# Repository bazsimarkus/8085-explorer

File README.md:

# 8085-explorer

A Netronics Explorer/85 compatible Intel 8085 single board computer that runs the original Microsoft ROM BASIC v4.7, the original Netronics Explorer/85 monitor ROM, and a custom MicroPython interpreter written entirely in 8085 assembly. Software compatible with the 1979 original, built from a minimal number of through-hole chips, and easy to assemble.

---

## Table of Contents

- [Overview](#overview)
- [Features](#features)
- [Getting Started](#getting-started)
  - [What You Need](#what-you-need)
  - [Flashing the ROM](#flashing-the-rom)
  - [Connecting](#connecting)
  - [Starting BASIC](#starting-basic)
- [MicroPython Interpreter](#micropython-interpreter)
  - [About](#about)
  - [Running MicroPython](#running-micropython)
  - [MicroPython Features](#micropython-features)
  - [Building from Source](#building-from-source)
- [Examples](#examples)
  - [Microsoft BASIC Examples](#microsoft-basic-examples)
  - [MicroPython Examples](#micropython-examples)
  - [Assembly Examples](#assembly-examples)
- [Schematic](#schematic)
  - [Bill of Materials](#bill-of-materials)
- [How It Works](#how-it-works)
  - [Address Bus Demultiplexing](#address-bus-demultiplexing)
  - [Memory Map](#memory-map)
  - [The Boot Problem and the Glue Logic](#the-boot-problem-and-the-glue-logic)
  - [Serial Communication](#serial-communication)
- [Documentation](#documentation)
- [Acknowledgments](#acknowledgments)
- [License](#license)

---

## Overview

The 8085 Explorer is a single board computer built around the Intel 8085 microprocessor. It is software compatible with the original Netronics Explorer/85 from 1979 and runs the same monitor ROM and Microsoft BASIC that shipped with the original kit. The board uses a small number of readily available through-hole chips and communicates through an RS232 serial port. Connect it to a terminal emulator like Tera Term and you have a working retro computer that boots into a machine language monitor and can run BASIC programs interactively.

In addition to the classic Microsoft BASIC environment, the board can also run a custom MicroPython interpreter written from scratch in 8085 assembly. Flash a different ROM image and the board boots into a Python-like interactive shell instead.

The design was inspired by Tom Nisbet's [Simple8085](https://github.com/TomNisbet/Simple8085). I used his [TommyPROM](https://github.com/TomNisbet/TommyPROM) programmer to flash the ROM image onto the 28C256 EEPROM.

---

## Features

- Intel 8085 CPU running at 3.072 MHz (6.144 MHz crystal divided by 2)
- 32K ROM (28C256 EEPROM) containing the Netronics monitor and Microsoft BASIC
- 32K Static RAM (HM62256BLP)
- RS232 serial port via MAX232 level converter and DB9 connector
- Bit-banged serial I/O using the 8085's SID and SOD pins
- Original Netronics Explorer/85 monitor ROM v1.4
- Microsoft ROM BASIC v4.7 (Copyright 1978 by Microsoft)
- Custom MicroPython interpreter (written in 8085 assembly, runs from a separate ROM image)
- Minimal chip count, all through-hole, easy to build on a soldering iron
- 9V DC barrel jack power input with L7805 5V regulator
- Power on reset with manual reset button
- Power LED, serial RX and TX activity LEDs
- Expansion header and SID/SOD pin headers
- Designed in KiCad, full schematic and PCB files included

---

## Getting Started

### What You Need

- The assembled 8085 Explorer board
- A 9V DC power supply (center positive, 2.1mm barrel jack)
- A DB9 serial cable or USB-to-RS232 adapter
- A terminal emulator (Tera Term, PuTTY, minicom, etc.)
- An EEPROM programmer for flashing the 28C256 (e.g. [TommyPROM](https://github.com/TomNisbet/TommyPROM))

### Flashing the ROM

The file `assets/msbasic47-rom-image.bin` contains the combined ROM image with both the Netronics monitor and Microsoft BASIC. Flash this file onto a 28C256 EEPROM using your programmer of choice.

Alternatively, flash `assets/micropython85/micropython85-rom-image.bin` to run the MicroPython interpreter instead.

### Connecting

1. Configure your terminal emulator for **9600 baud, 8 data bits, no parity, 1 stop bit (9600 8N1)**.
2. Connect the serial cable between the board's DB9 port and your computer.
3. Flip the power switch on.
4. If using the Microsoft BASIC ROM: press the Space key once. The monitor ROM uses this first character to auto-detect the baud rate. Nothing will appear on screen until you do this.
5. If using the MicroPython ROM: the interpreter boots directly and presents a `>>>` prompt.

After pressing Space (with the BASIC ROM), you should see the Explorer/85 monitor banner:

```
EXPLORER-85    VER 1.4
Copyright 1979
Netronics R&D
New Milford, CT.
```

### Starting BASIC

From the monitor prompt, configure the memory map and jump to BASIC:

```
.XS 44FF-7800 FFFF-C000
.G
```

BASIC will ask for memory size and terminal width. Press Enter to accept the defaults, or type values:

```
Memory size? 30000
Terminal width? 72
Microsoft ROM BASIC Ver 4.7
Copyright (C) 1978 by Microsoft
29443 Bytes free
Ok
```

You are now in BASIC and can write and run programs interactively.

Note: In my experience there is no whitespace between a monitor command and its parameter. For example, `GC000` starts BASIC (jumps to address C000h), not `G C000`.

---

## MicroPython Interpreter

### About

The MicroPython interpreter is a minimal Python-like environment written entirely in 8085 assembly. It is not a port of the official MicroPython project. It is a from-scratch implementation that provides a familiar interactive experience on an 8-bit processor with no operating system.

The interpreter lives in a separate ROM image. You swap between Microsoft BASIC and MicroPython by flashing a different binary onto the 28C256.

### Running MicroPython

Flash `assets/micropython85/micropython85-rom-image.bin` onto your 28C256, insert the chip, and power on. The board boots directly into the REPL:

```
8085-Explorer Booting...
Memory Swap Successful: ROM@8000, RAM@0000
Booting MicroPython v1.20.0-8085 on 2026-05-10; 8085-Explorer with i8085
Type "help()" for more information.

>>> print("Hello world!")
Hello world!
>>>
```

### MicroPython Features

- Interactive REPL with `>>>` prompt and `...` continuation for blocks
- 26 variables (a through z), each a 16-bit signed integer
- Arithmetic: `+` `-` `*` `/` `//` `**` `%`
- Comparisons: `>` `<` `>=` `<=` `==` `!=`
- `print()` with string literals and numeric expressions, comma-separated
- `if/else` blocks with indentation
- `for i in range(n)` and `for i in range(start, stop)` loops
- `help()` built-in
- Comments with `#`
- Error reporting: `SyntaxError` and `ZeroDivisionError`

### Building from Source

The full source is at `assets/micropython85/micropython85.asm`. Assemble it with [Tom Nisbet's asm85](https://github.com/TomNisbet/asm85):

```
asm85 -b 8000:ffff micropython85.asm
```

This produces the binary ROM image ready for flashing.

---

## Examples

The `examples/` directory contains programs for the three levels of the system.

### Microsoft BASIC Examples

Located in `examples/basic/`. These programs are typed in (or pasted) at the `Ok` prompt when the board is running the Microsoft ROM BASIC image.

### MicroPython Examples

Located in `examples/micropython/`. These scripts are typed in (or pasted) at the `>>>` prompt when the board is running the MicroPython interpreter ROM image.

### Assembly Examples

Located in `examples/assembly/`. These are standalone 8085 assembly programs that get assembled with [asm85](https://github.com/TomNisbet/asm85) and flashed directly onto the 28C256. Unlike the BASIC and MicroPython examples (which run inside their respective interpreters), assembly programs replace the entire ROM content and run on bare hardware.

To build and flash:

```
asm85 -b 8000:ffff yourprogram.asm
```

Then program the resulting binary onto a 28C256 EEPROM.

---

## Schematic

The full KiCad project files (schematic, PCB layout, and project file) are in the `schematic/` directory.

### Bill of Materials

The following table lists all components needed to build one complete 8085 Explorer board.

#### PCB

| Ref | Qty | Description |
|-----|-----|-------------|
| - | 1 | 8085 Explorer v1.0 PCB |

#### Integrated Circuits

| Ref | Qty | Value | Package |
|-----|-----|-------|---------|
| U1 | 1 | 8085 | DIP-40 |
| U2 | 1 | 74LS573 | DIP-20 |
| U3 | 1 | 28C256 EEPROM | DIP-28 |
| U4 | 1 | HM62256BLP SRAM | DIP-28 |
| U5 | 1 | 74LS14 | DIP-14 |
| U6 | 1 | 74LS32 | DIP-14 |
| U7 | 1 | 74LS74 | DIP-14 |
| U8 | 1 | MAX232 | DIP-16 |
| U9 | 1 | L7805 voltage regulator | TO-220 |

#### IC Sockets

| Qty | Description |
|-----|-------------|
| 1 | 40-pin DIP socket (for U1) |
| 1 | 20-pin DIP socket (for U2) |
| 2 | 28-pin DIP socket (for U3, U4) |
| 3 | 14-pin DIP socket (for U5, U6, U7) |
| 1 | 16-pin DIP socket (for U8) |

#### Capacitors

| Ref | Qty | Value | Type |
|-----|-----|-------|------|
| C1-C7, C17 | 7 | 100nF | Ceramic |
| C8 | 1 | 22pF | Ceramic |
| C9 | 1 | 47uF | Electrolytic |
| C10-C14 | 5 | 1uF | Electrolytic |
| C15, C18 | 2 | 10uF | Electrolytic |
| C16 | 1 | 330nF | Ceramic |

#### Resistors

| Ref | Qty | Value |
|-----|-----|-------|
| R1, R2, R6 | 3 | 1k |
| R3, R4, R5 | 3 | 10k |

#### Diodes & LEDs

| Ref | Qty | Value |
|-----|-----|-------|
| D1 | 1 | LED 5mm Yellow |
| D2 | 1 | LED 5mm Green |
| D3, D5 | 2 | 1N4001 |
| D4 | 1 | LED 5mm Red |

#### Crystal

| Ref | Qty | Value |
|-----|-----|-------|
| Y1 | 1 | 6.144 MHz (HC49-U) |

#### Connectors & Switches

| Ref | Qty | Description |
|-----|-----|-------------|
| J1 | 1 | DB9 female connector (DE9, right-angle PCB mount) |
| J2 | 1 | DC-005 barrel jack (2.1mm center positive) |
| J4, J5 | 2 | 1x2 pin header (2.54mm) |
| J6 | 1 | 2x5 pin socket (2.54mm, expansion header) |
| S1 | 1 | Tactile push button 6x6mm (reset) |
| S2 | 1 | Toggle switch 7x7mm (power) |

#### Thermal Management

| Qty | Description |
|-----|-------------|
| 1 | Heatsink for TO-220 (for L7805 U9) |

#### External / Off-Board Items

| Qty | Description |
|-----|-------------|
| 1 | 9V DC power supply (center positive, 2.1mm barrel jack) |
| 1 | RS-232 to USB cable (DB9 male to USB-A) |
| 4 | Rubber feet, 3M SJ61A6 |

---

## How It Works

The 8085 Explorer uses a small amount of glue logic to decode memory addresses and manage access to the ROM and RAM chips. If you are new to computer hardware, the following sections explain every piece of the design.

### Address Bus Demultiplexing

The 8085 multiplexes the lower 8 bits of the address bus (A0 to A7) with the data bus (D0 to D7) on the same physical pins. A 74LS573 octal latch (U2) captures the lower address bits when the ALE (Address Latch Enable) signal goes high. After the latch captures them, the bus is free to carry data. This gives us a full 16-bit address bus separated from the 8-bit data bus.

### Memory Map

Once the boot sequence is complete (see below), the memory is split into two halves using address line A15:

- `0000h` to `7FFFh` : 32K RAM (HM62256BLP)
- `8000h` to `FFFFh` : 32K ROM (28C256 EEPROM)

When A15 is low, RAM is selected. When A15 is high, ROM is selected. The monitor lives at F800h and Microsoft BASIC starts at C000h, both in the upper ROM half.

### The Boot Problem and the Glue Logic

If you are a beginner, your first instinct might be: just wire A15 directly to the chip enable pins, select ROM when A15 is high, select RAM when A15 is low. That would work for normal operation. But it creates a problem at startup.

When the 8085 resets, it always fetches its first instruction from address 0000h. If RAM is at 0000h, the CPU reads random garbage from the uninitialized RAM and crashes immediately. The CPU must see ROM at address 0000h when it first powers on.

But we cannot permanently place ROM at 0000h either. Microsoft BASIC and other 8080/8085 software assume that RAM starts at address 0000h. They use the lowest addresses for the stack, variables, and hardware interrupt vectors. If ROM occupied the bottom of memory permanently, BASIC would try to write its variables into ROM and fail.

So we have two conflicting requirements:
1. ROM must be at 0000h at power-on so the CPU can boot.
2. RAM must be at 0000h during normal operation so software works correctly.

The glue logic on this board solves this with a temporary override at reset.

**The Reset Condition Flip-Flop (U7, 74LS74)**

A 74LS74 D flip-flop acts as a one-bit "boot mode" flag. When the CPU resets, its RESET_OUT signal clocks the flip-flop, forcing its Q output high. As long as Q is high, the system is in boot mode.

**Boot Mode Behavior (U6, 74LS32 OR gates and U5, 74LS14 inverters)**

The OR gates enforce this rule: ROM is selected if the flip-flop is set OR if A15 is high. RAM is selected only when neither condition is true. The IO/M signal from the CPU disables both memory chips during I/O operations.

So at power-on, with the flip-flop set, the logic forces ROM to be active regardless of A15. The CPU asks for address 0000h and gets ROM. The first instruction in the ROM image is a jump to address F800h (where the monitor actually lives in the upper half of memory).

**Exiting Boot Mode**

When the CPU executes that jump and reads from the upper memory (A15 goes high), the logic detects a read operation with A15 high and clears the flip-flop. Boot mode ends. From this point forward, A15 alone controls memory selection: low for RAM, high for ROM.

Because the CPU is already executing code in the ROM at F800h, it does not notice that the bottom 32K just switched from ROM to RAM. The memory map is now in its normal configuration. When you later type `GC000` to start BASIC, BASIC wakes up, scans the lower memory, finds 32K of RAM starting at 0000h, and uses it for your programs and variables.

Without these few logic gates and the flip-flop, classic 8085 software like Microsoft BASIC simply would not work on this board.

### Serial Communication

Serial communication is handled through the 8085's built-in SID (Serial Input Data) and SOD (Serial Output Data) pins. The monitor ROM implements a bit-banged UART in software. A MAX232 chip (U8) converts the TTL level signals to proper RS232 voltage levels for the DB9 connector.

The monitor does not use a fixed baud rate. Instead, after reset it waits for you to press the Space key and measures the timing of that character to auto-detect the baud rate. This means the board works at whatever speed your terminal is configured for. I use 9600 bps.

The MicroPython interpreter ROM uses its own bit-banged serial routines hardcoded to 9600 baud (tuned for the 6.144 MHz crystal). It does not require a Space keypress at startup.

---

## Documentation

The `docs/netronics-explorer-85/` directory contains scanned original documentation and photos from the Netronics Explorer/85:

- Original manual pages (Netronics_Explorer85_A through E)
- Terminal ROM user information
- Cabinet assembly instructions and photos
- Original ROM images for the monitor (`explorer_monitor_rom/EXPLORER.HEX`) and BASIC (`explorer_basic_roms/C000.HEX` through `D800.HEX`) as separate files matching the smaller ROM chips used in the original hardware

---

## Acknowledgments

- Tom Nisbet for [Simple8085](https://github.com/TomNisbet/Simple8085), which was the main inspiration for this project, for [TommyPROM](https://github.com/TomNisbet/TommyPROM), which I used to program the EEPROM, and for [asm85](https://github.com/TomNisbet/asm85), the assembler used to build the MicroPython interpreter
- Netronics R&D for the original Explorer/85 design and monitor ROM
- Microsoft for ROM BASIC v4.7

---

## License

The original Netronics monitor ROM and Microsoft BASIC ROM images are included for educational and preservation purposes.

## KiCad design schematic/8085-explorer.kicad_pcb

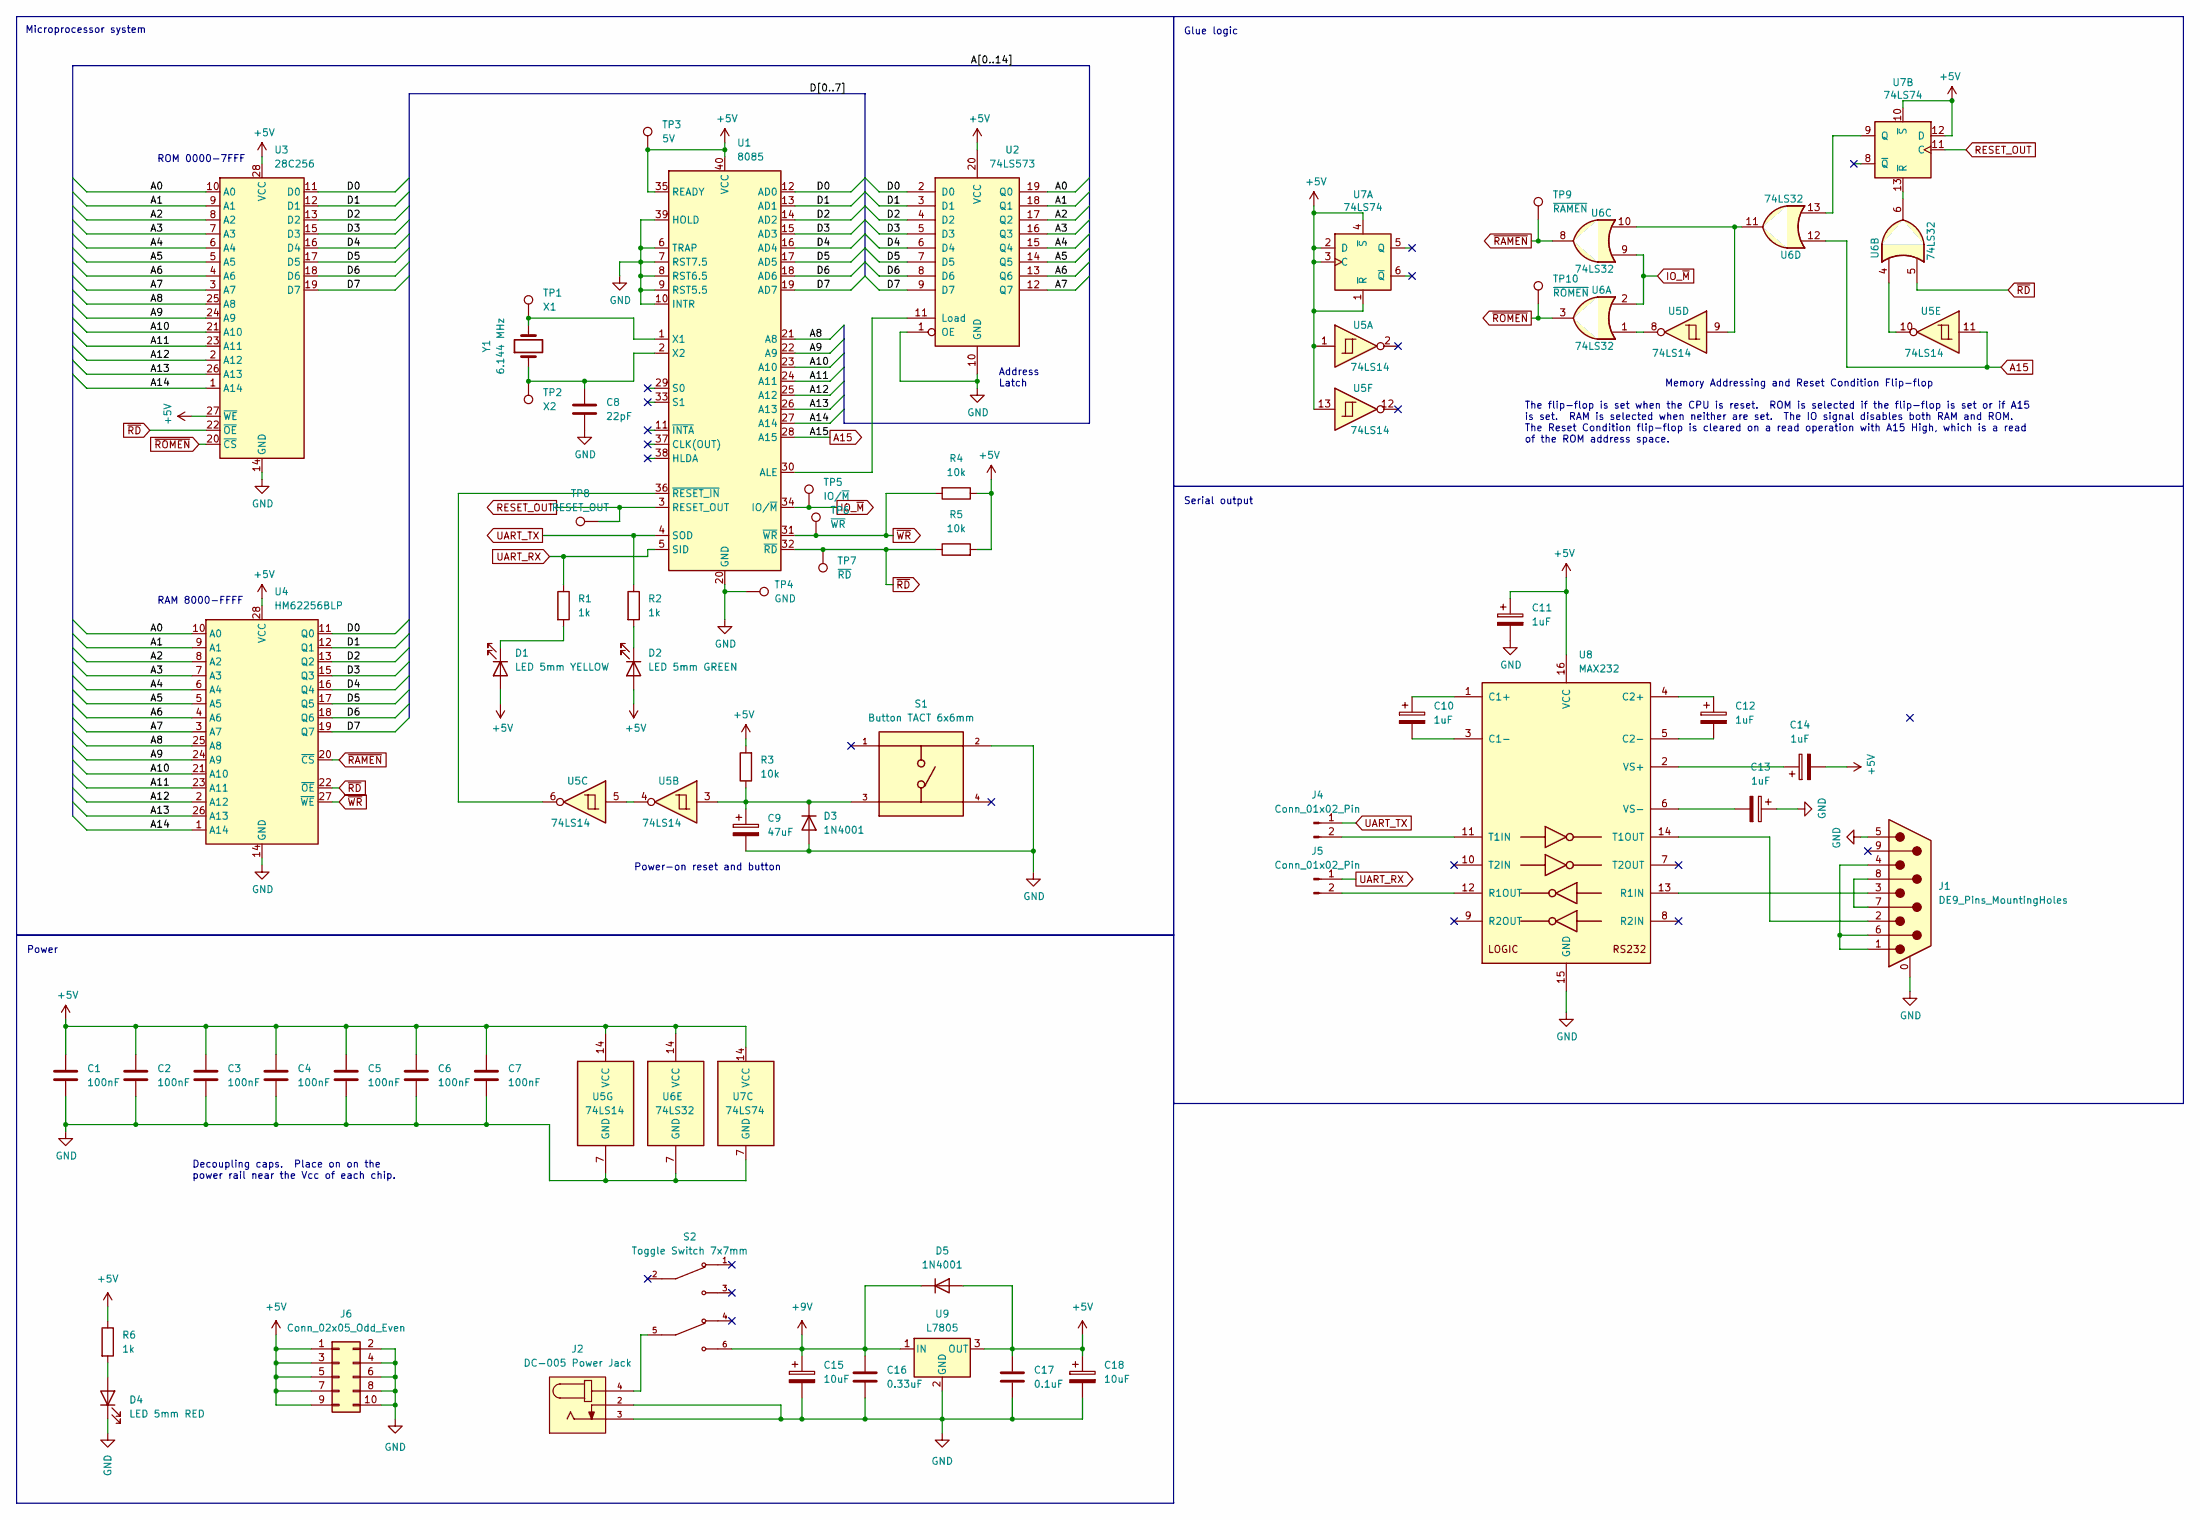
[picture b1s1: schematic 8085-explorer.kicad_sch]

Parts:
C1, C2, C3, C4, C5, C6, C7: 100nF; C_100nF_L7.0mm_W2.5mm_P5.00mm
C8: 22pF; C_Rect_L4.6mm_W2.0mm_P2.50mm_MKS02_FKP02
C9: 47uF; CP_Radial_D4.0mm_P2.00mm
C10, C11, C12, C13, C14: 1uF; CP_Radial_D4.0mm_P2.00mm
C15, C18: 10uF; CP_Radial_D4.0mm_P2.00mm
C16: 0.33uF; C_100nF_L7.0mm_W2.5mm_P5.00mm
C17: 0.1uF; C_100nF_L7.0mm_W2.5mm_P5.00mm
D1: LED 5mm YELLOW; LED_D5.0mm_YELLOW
D2: LED 5mm GREEN; LED_D5.0mm_GREEN
D3, D5: 1N4001; D_DO-41_SOD81_P10.16mm_Horizontal
D4: LED 5mm RED; LED_D5.0mm_RED
J1: DE9_Pins_MountingHoles; DSUB-9_Socket_Horizontal_P2.77x2.84mm_EdgePinOffset9.90mm_H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
J2: DC-005 Power Jack
J4, J5: Conn_01x02_Pin; PinHeader_1x02_P2.54mm_Vertical
J6: Conn_02x05_Odd_Even; PinSocket_2x05_P2.54mm_Vertical
R1, R2, R6: 1k; R_1k_Axial_DIN0207
R3, R4, R5: 10k; R_10k_Axial_DIN0207
S1: Button TACT 6x6mm; PARTREV 1.0
S2: Toggle Switch 7x7mm; PARTREV E; DigiKey_Part_Number EG6032-ND
TP1: X1; TestPoint_THTPad_D1.0mm_Drill0.5mm
TP2: X2; TestPoint_THTPad_D1.0mm_Drill0.5mm
TP3: 5V; TestPoint_THTPad_D1.0mm_Drill0.5mm
TP4: GND; TestPoint_THTPad_D1.0mm_Drill0.5mm
TP5: IO/~{M}; TestPoint_THTPad_D1.0mm_Drill0.5mm
TP6: ~{WR}; TestPoint_THTPad_D1.0mm_Drill0.5mm
TP7: ~{RD}; TestPoint_THTPad_D1.0mm_Drill0.5mm
TP8: RESET_OUT; TestPoint_THTPad_D1.0mm_Drill0.5mm
TP9: ~{RAMEN}; TestPoint_THTPad_D1.0mm_Drill0.5mm
TP10: ~{ROMEN}; TestPoint_THTPad_D1.0mm_Drill0.5mm
U1: 8085; DIP-40_W15.24mm
U2: 74LS573; DIP-20_W7.62mm
U3: 28C256; DIP-28_W15.24mm
U4: HM62256BLP; DIP-28_W15.24mm
U5: 74LS14; DIP-14_W7.62mm
U6: 74LS32; DIP-14_W7.62mm
U7: 74LS74; DIP-14_W7.62mm
U8: MAX232; DIP-16_W7.62mm
U9: L7805; TO-220-3_Vertical
Y1: 6.144 MHz; Crystal_HC49-U_Vertical

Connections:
+5V: C1.1, C2.1, C3.1, C4.1, C5.1, C6.1, C7.1, C11.1, C14.2, C17.2, C18.1, D1.2 (A), D2.2 (A), D5.2 (A), J6.1, J6.3, J6.5, J6.7, J6.9, R3.2, R4.1, R5.2, R6.1, TP3.1, U1.35 (READY), U1.40 (VCC), U2.20 (VCC), U3.27 (~WE), U3.28 (VCC), U4.28 (VCC), U5.1, U5.13, U5.14 (VCC), U6.14 (VCC), U7.1 (~R), U7.2 (D), U7.3 (C), U7.4 (~S), U7.10 (~S), U7.12 (D), U7.14 (VCC), U8.16 (VCC), U9.3 (OUT)
+9V: C15.1, C16.2, D5.1 (K), S2.6, U9.1 (IN)
/A0: U2.19 (Q0), U3.10 (A0), U4.10 (A0)
/A1: U2.18 (Q1), U3.9 (A1), U4.9 (A1)
/A2: U2.17 (Q2), U3.8 (A2), U4.8 (A2)
/A3: U2.16 (Q3), U3.7 (A3), U4.7 (A3)
/A4: U2.15 (Q4), U3.6 (A4), U4.6 (A4)
/A5: U2.14 (Q5), U3.5 (A5), U4.5 (A5)
/A6: U2.13 (Q6), U3.4 (A6), U4.4 (A6)
/A7: U2.12 (Q7), U3.3 (A7), U4.3 (A7)
/A8: U1.21 (A8), U3.25 (A8), U4.25 (A8)
/A9: U1.22 (A9), U3.24 (A9), U4.24 (A9)
/A10: U1.23 (A10), U3.21 (A10), U4.21 (A10)
/A11: U1.24 (A11), U3.23 (A11), U4.23 (A11)
/A12: U1.25 (A12), U3.2 (A12), U4.2 (A12)
/A13: U1.26 (A13), U3.26 (A13), U4.26 (A13)
/A14: U1.27 (A14), U3.1 (A14), U4.1 (A14)
/D0: U1.12 (AD0), U2.2 (D0), U3.11 (D0), U4.11 (Q0)
/D1: U1.13 (AD1), U2.3 (D1), U3.12 (D1), U4.12 (Q1)
/D2: U1.14 (AD2), U2.4 (D2), U3.13 (D2), U4.13 (Q2)
/D3: U1.15 (AD3), U2.5 (D3), U3.15 (D3), U4.15 (Q3)
/D4: U1.16 (AD4), U2.6 (D4), U3.16 (D4), U4.16 (Q4)
/D5: U1.17 (AD5), U2.7 (D5), U3.17 (D5), U4.17 (Q5)
/D6: U1.18 (AD6), U2.8 (D6), U3.18 (D6), U4.18 (Q6)
/D7: U1.19 (AD7), U2.9 (D7), U3.19 (D7), U4.19 (Q7)
A15: U1.28 (A15), U5.11, U6.12
GND: C1.2, C2.2, C3.2, C4.2, C5.2, C6.2, C7.2, C8.2, C9.2, C11.2, C13.1, C15.2, C16.1, C17.1, C18.2, D3.2 (A), D4.1 (K), J1.0 (PAD), J1.5, J2.2, J2.3, J6.2, J6.4, J6.6, J6.8, J6.10, S1.2, TP4.1, U1.6 (TRAP), U1.7 (RST7.5), U1.8 (RST6.5), U1.9 (RST5.5), U1.10 (INTR), U1.20 (GND), U1.39 (HOLD), U2.1 (OE), U2.10 (GND), U3.14 (GND), U4.14 (GND), U5.7 (GND), U6.7 (GND), U7.7 (GND), U8.15 (GND), U9.2 (GND)
IO_~M: TP5.1, U1.34 (IO/~M), U6.2, U6.9
unnamed: D1.1 (K), R1.2
unnamed: D2.1 (K), R2.2
unnamed: C9.1, D3.1 (K), R3.1, S1.3, U5.3
unnamed: D4.2 (A), R6.2
unnamed: J1.1, J1.4, J1.6
unnamed: J1.7, J1.8
unnamed: J2.4, S2.5
unnamed: J4.2, U8.11 (T1IN)
unnamed: J5.2, U8.12 (R1OUT)
unnamed: U1.30 (ALE), U2.11 (Load)
unnamed: TP1.1, U1.1 (X1), Y1.2
unnamed: C8.1, TP2.1, U1.2 (X2), Y1.1
unnamed: U1.36 (~RESET_IN), U5.6
unnamed: U5.4, U5.5
unnamed: U5.8, U6.1
unnamed: U5.9, U6.10, U6.11
unnamed: U5.10, U6.4
unnamed: U6.13, U7.9 (Q)
unnamed: U6.6, U7.13 (~R)
unnamed: C10.1, U8.1 (C1+)
unnamed: C10.2, U8.3 (C1-)
unnamed: C12.1, U8.4 (C2+)
unnamed: C12.2, U8.5 (C2-)
unnamed: J1.3, U8.13 (R1IN)
unnamed: J1.2, U8.14 (T1OUT)
unnamed: C14.1, U8.2 (VS+)
unnamed: C13.2, U8.6 (VS-)
RESET_OUT: TP8.1, U1.3 (RESET_OUT), U7.11 (C)
UART_RX: J5.1, R1.1, U1.5 (SID)
UART_TX: J4.1, R2.1, U1.4 (SOD)
~RAMEN: TP9.1, U4.20 (~CS), U6.8
~RD: R5.1, TP7.1, U1.32 (~RD), U3.22 (~OE), U4.22 (~OE), U6.5
~ROMEN: TP10.1, U3.20 (~CS), U6.3
~WR: R4.2, TP6.1, U1.31 (~WR), U4.27 (~WE)

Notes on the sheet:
Address Latch
Microprocessor system
The flip-flop is set when the CPU is reset. ROM is selected if the flip-flop is set or if A15 is set. RAM is selected when neither are set. The IO signal disables both RAM and ROM. The Reset Condition flip-flop is cleared on a read operation with A15 High, which is a read of the ROM address space.
Decoupling caps. Place on on the power rail near the Vcc of each chip.
RAM 8000-FFFF
Glue logic
Serial output
Memory Addressing and Reset Condition Flip-flop
ROM 0000-7FFF
Power-on reset and button
Power

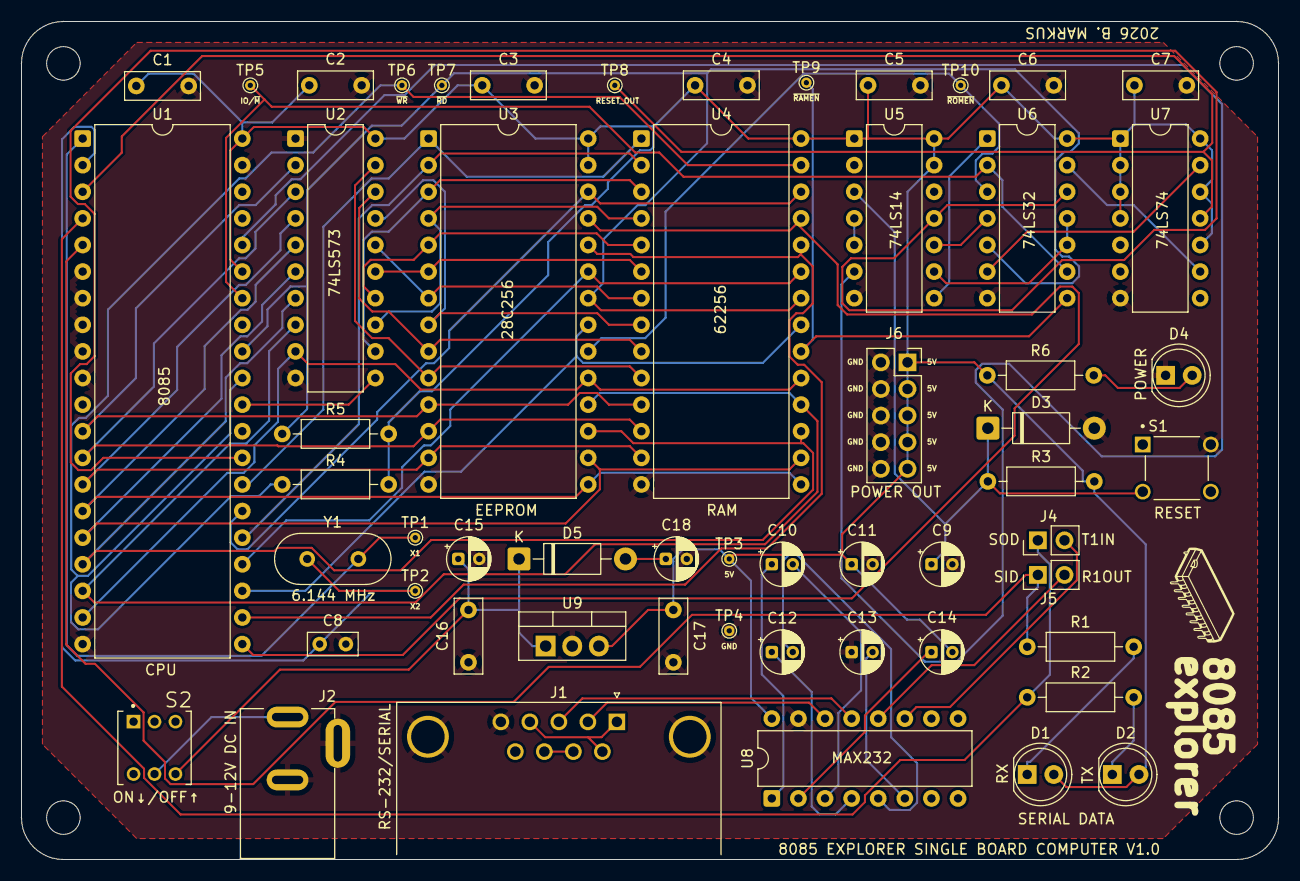
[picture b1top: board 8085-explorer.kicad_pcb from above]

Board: 2 copper layers, 120.0 x 80.0 mm, 61 parts (0 on the bottom side), 62 nets.

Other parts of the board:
G1: LOGO
MH1, MH2, MH3, MH4: MountingHole_3.2mm_M3_DIN965

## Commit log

2026-03-17 Schematic updated
2026-03-17 PCB updated
2026-05-09 Images added
2026-05-09 28C256 ROM image and original Netronics Explorer-85 documentation added
2026-05-09 Hello World example application added to examples folder
2026-05-09 BASIC example programs added
2026-05-10 MicroPython ASM source code and ROM image added, examples reorganized
2026-05-10 Examples updated
2026-05-10 Fix file casing for BASIC examples
